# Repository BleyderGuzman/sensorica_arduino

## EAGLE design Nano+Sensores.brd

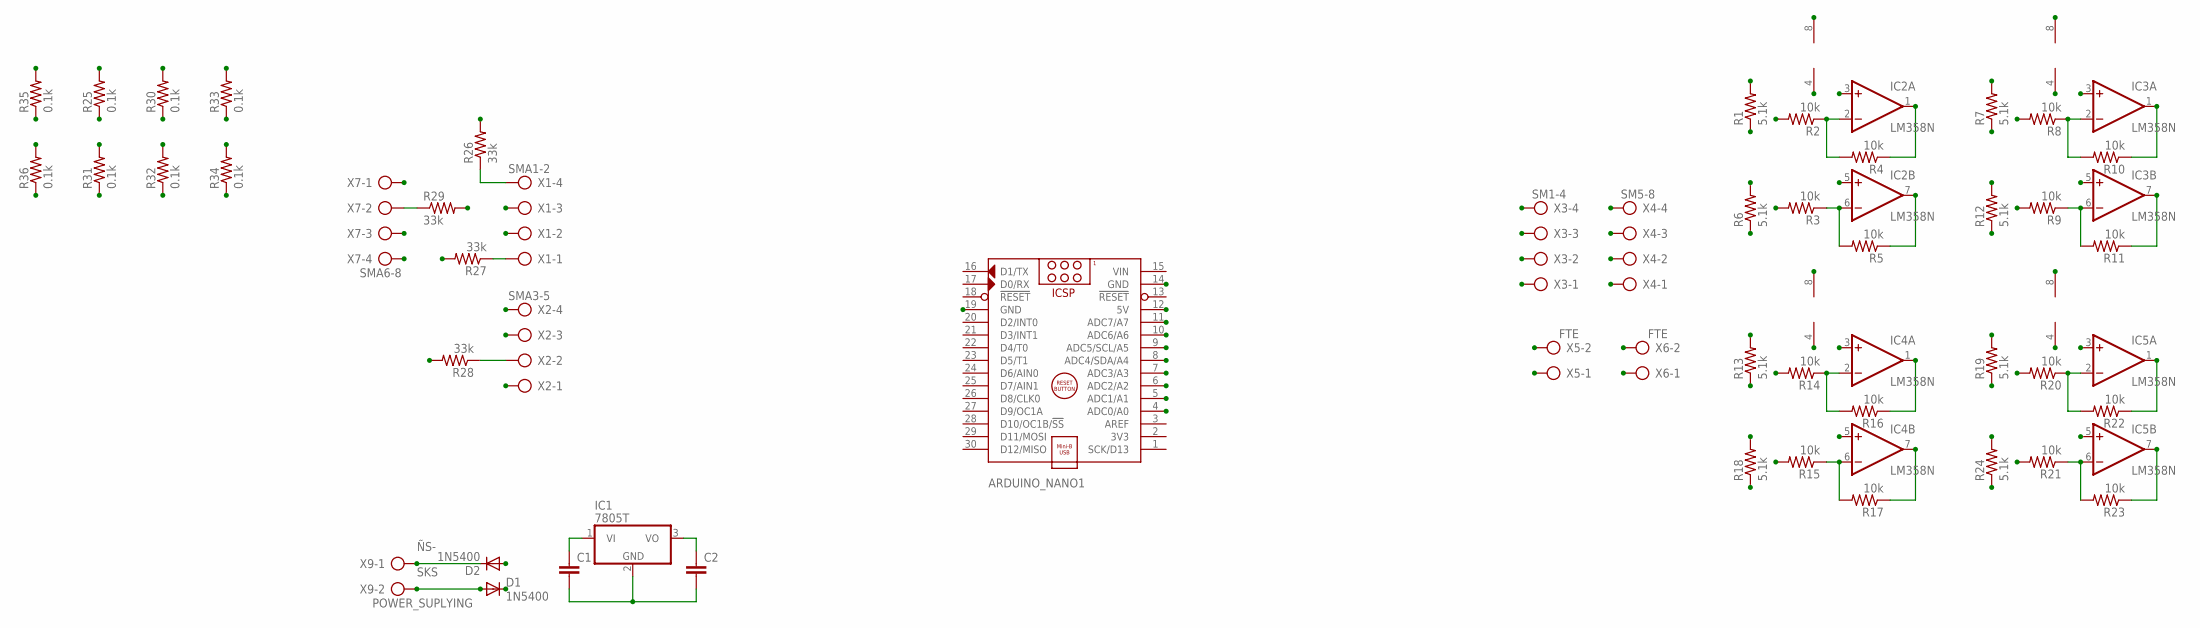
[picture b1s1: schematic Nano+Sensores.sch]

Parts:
ARDUINO_NANO1: ARDUINO_NANO
C1, C2: C-EU025-025X050; C025-025X050
D1, D2: 1N5400; DO201-15
IC1: 7805T; TO220H
IC2, IC3, IC4, IC5: LM358N; DIL08
R1, R6, R7, R12, R13, R18, R19, R24: 5.1k; 0204/5
R2, R3, R4, R5, R8, R9, R10, R11, R14, R15, R16, R17, R20, R21, R22, R23: 10k; 0204/5
R25, R30, R31, R32, R33, R34, R35, R36: 0.1k; 0204/5
R26, R27, R28, R29: 33k; 0204/5
X1: SMA1-2; AK300/4
X2: SMA3-5; AK300/4
X3: SM1-4; AK300/4
X4: SM5-8; AK300/4
X5, X6: FTE; AK300/2
X7: SMA6-8; AK300/4
X9: POWER_SUPLYING; AK300/2

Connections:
+5V: ARDUINO_NANO1.12 (5V), C2.1, IC1.3 (VO), IC2.8 (V+), IC3.8 (V+), IC4.8 (V+), IC5.8 (V+), R1.2, R6.2, R7.2, R12.2, R13.2, R18.2, R19.2, R24.2, R25.2, R30.2, R31.2, R32.2, R33.2, R34.2, R35.2, R36.2
+12V: C1.1, D1.C, IC1.1 (VI), X5.2, X6.2
A0: ARDUINO_NANO1.4 (ADC0/A0), IC2.1 (OUT), R4.1
A1: ARDUINO_NANO1.5 (ADC1/A1), IC2.7 (OUT), R5.1
A2: ARDUINO_NANO1.6 (ADC2/A2), IC3.1 (OUT), R10.1
A3: ARDUINO_NANO1.7 (ADC3/A3), IC3.7 (OUT), R11.1
A4: ARDUINO_NANO1.8 (ADC4/SDA/A4), IC4.1 (OUT), R16.1
A5: ARDUINO_NANO1.9 (ADC5/SCL/A5), IC4.7 (OUT), R17.1
A6: ARDUINO_NANO1.10 (ADC6/A6), IC5.1 (OUT), R22.1
A7: ARDUINO_NANO1.11 (ADC7/A7), IC5.7 (OUT), R23.1
GND: ARDUINO_NANO1.14 (GND), ARDUINO_NANO1.19 (GND), C1.2, C2.2, D2.A, IC1.2 (GND), IC2.3 (+IN), IC2.4 (V-), IC2.5 (+IN), IC3.3 (+IN), IC3.4 (V-), IC3.5 (+IN), IC4.3 (+IN), IC4.4 (V-), IC4.5 (+IN), IC5.3 (+IN), IC5.4 (V-), IC5.5 (+IN), R26.2, R27.2, R28.2, R29.2, X5.1, X6.1
unnamed: IC2.2 (-IN), R2.1, R4.2
unnamed: R27.1, X1.1
unnamed: R29.1, X7.2
unnamed: IC2.6 (-IN), R3.1, R5.2
unnamed: IC3.2 (-IN), R8.1, R10.2
unnamed: R26.1, X1.4
unnamed: R28.1, X2.2
unnamed: IC3.6 (-IN), R9.1, R11.2
unnamed: IC4.2 (-IN), R14.1, R16.2
unnamed: IC4.6 (-IN), R15.1, R17.2
unnamed: IC5.2 (-IN), R20.1, R22.2
unnamed: IC5.6 (-IN), R21.1, R23.2
SG_SM1: R1.1, R2.2, X3.4
SG_SM2: R3.2, R6.1, X3.3
SG_SM3: R7.1, R8.2, X3.2
SG_SM4: R9.2, R12.1, X3.1
SG_SM5: R13.1, R14.2, X4.4
SG_SM6: R15.2, R18.1, X4.3
SG_SM7: R19.1, R20.2, X4.2
SG_SM8: R21.2, R24.1, X4.1
SKS: D1.A, X9.2
SMA1: R25.1, X1.3
SMA2: R30.1, X1.2
SMA3: R33.1, X2.4
SMA4: R31.1, X2.3
SMA5: R32.1, X2.1
SMA6: R34.1, X7.1
SMA7: R35.1, X7.3
SMA8: R36.1, X7.4
VIN: ARDUINO_NANO1.15 (VIN)
ÑS-: D2.C, X9.1

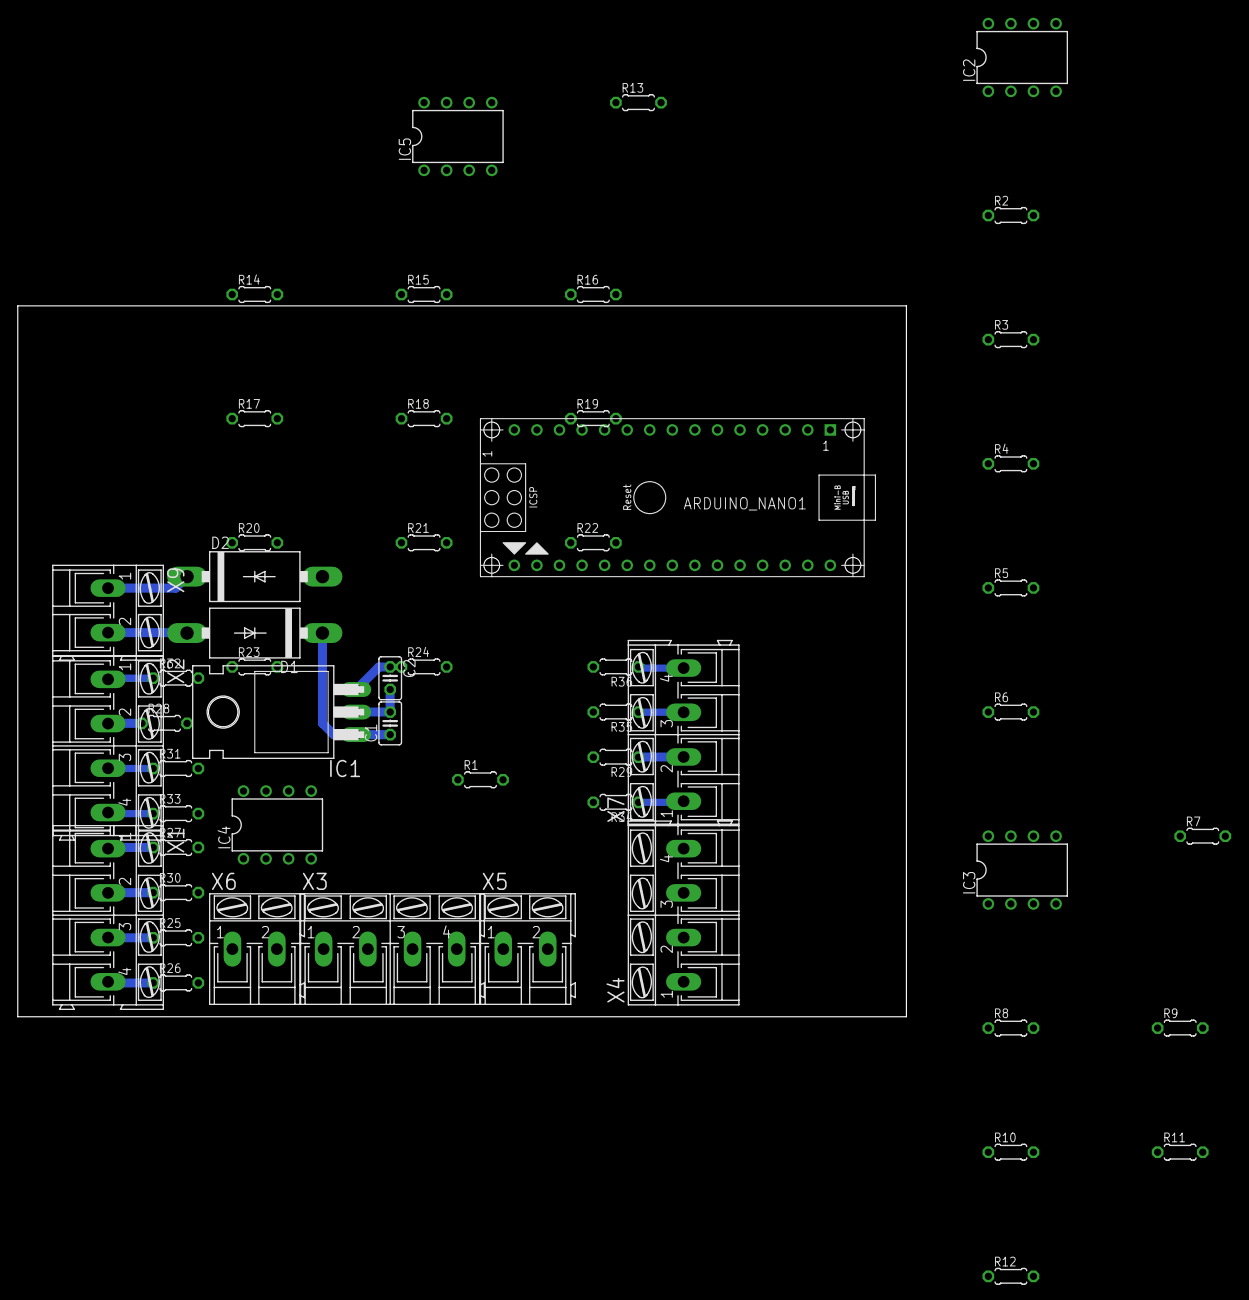
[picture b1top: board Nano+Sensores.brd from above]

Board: 2 copper layers, 100.0 x 80.0 mm, 54 parts (0 on the bottom side), 41 nets.
